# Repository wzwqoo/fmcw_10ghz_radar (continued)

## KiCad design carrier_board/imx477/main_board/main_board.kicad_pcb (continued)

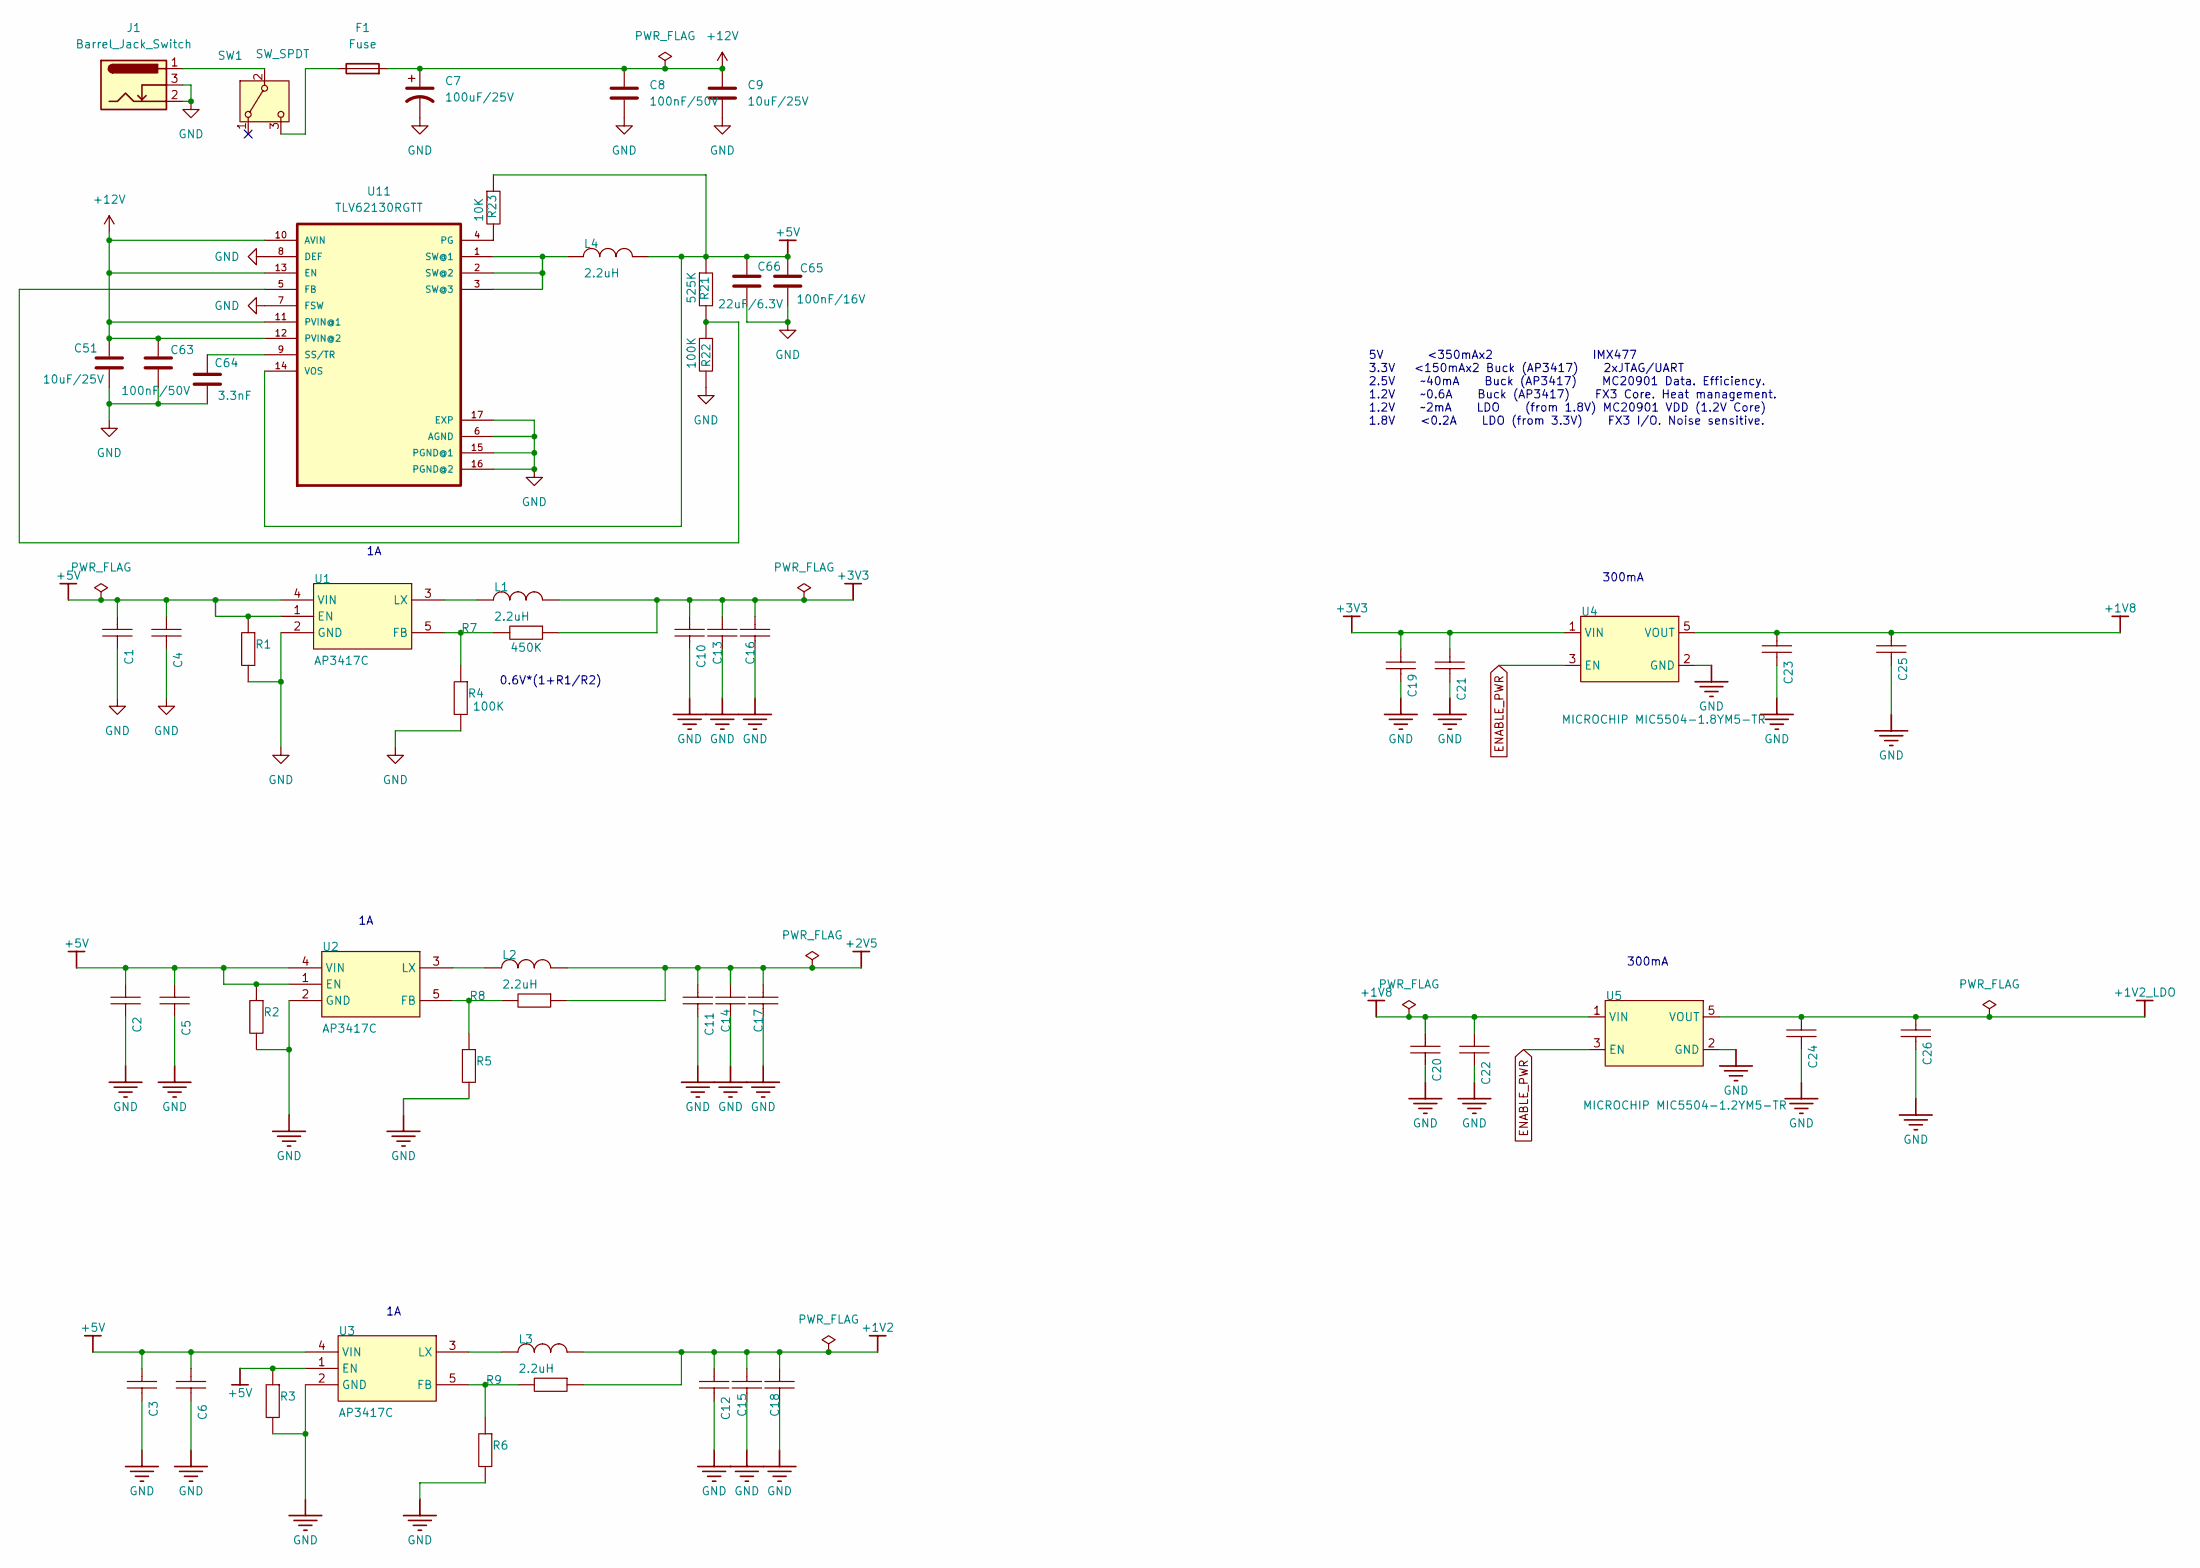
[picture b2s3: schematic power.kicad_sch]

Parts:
C1, C2, C3, C19, C20, C25, C26: 10uF; C_0603_1608Metric; RATINGS 50V; NP0; MANUFACTURER PART NUMBE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 06035A561JAT2A
C4, C5, C6, C10, C11, C12, C21, C22, C23, C24: 100nF; C_0603_1608Metric; TOLERANCE ±10%; RATINGS 16V; X7R; MANUFACTURER PART NUMBE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 CC0402KRX7R7BB103
C7: 100uF/25V; CP_Elec_6.3x5.7
C8, C63: 100nF/50V; C_0603_1608Metric
C9, C51: 10uF/25V; C_0603_1608Metric
C13, C14, C15, C16, C17, C18: 10uF; C_0603_1608Metric; TOLERANCE ±10%; RATINGS 16V; X5R; MANUFACTURER PART NUMBE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 EMK212BJ475KG-T
C64: 3.3nF; C_0603_1608Metric
C65: 100nF/16V; C_0603_1608Metric
C66: 22uF/6.3V; C_0603_1608Metric
F1: Fuse; Fuse_1812_4532Metric; Part# SMD1812P200TF16; LCSC Part # C20812
J1: Barrel_Jack_Switch; BarrelJack_CLIFF_FC681465S_SMT_Horizontal; Part# TBD
L1, L2, L3, L4: 2.2uH; L_Taiyo-Yuden_MD-4040; Part# CMLO0420H2R2MTT; LCSC Part # C438930
R1, R2, R3, R23: 10K; R_0603_1608Metric; RATINGS 1/16 W; TOLERANCE ±5%; MANUFACTURER PART NUMBE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 RC0402JR-073K3L
R4, R5, R6, R9, R22: 100K; R_0603_1608Metric; RATINGS 1/16 W; TOLERANCE ±5%; MANUFACTURER PART NUMBE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 RC0402JR-073K3L
R7: 450K; R_0603_1608Metric; RATINGS 1/16 W; TOLERANCE ±5%; MANUFACTURER PART NUMBE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 RC0402JR-073K3L
R8: 320K; R_0603_1608Metric; RATINGS 1/16 W; TOLERANCE ±5%; MANUFACTURER PART NUMBE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 RC0402JR-073K3L
R21: 525K; R_0603_1608Metric; RATINGS 1/16 W; TOLERANCE ±5%; MANUFACTURER PART NUMBE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 RC0402JR-073K3L
SW1: SW_SPDT; SW_SPDT_CK_JS102011SAQN; Part# JS102011SAQN; LCSC Part # C221660
U1, U2, U3: AP3417C; SOT-23-5; Part# AP3417CKTR-G1; LCSC Part # C500759
U4: MICROCHIP MIC5504-1.8YM5-TR; SOT-23-5; Part# MIC5504-1.8YM5-TR; LCSC Part # C626116
U5: MICROCHIP MIC5504-1.2YM5-TR; SOT-23-5; Part# MIC5504-1.8YM5-TR; LCSC Part # C626116
U11: TLV62130RGTT; VQFN-16-1EP_3x3mm_P0.5mm_EP1.6x1.6mm; DigiKey_Part_Number 296-32407-1-ND

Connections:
+1V2: C12.2, C15.1, C18.1, L3.2, R9.2; also elsewhere on the board
+1V2_LDO: C24.2, C26.1, U5.5 (VOUT); also elsewhere on the board
+1V8: C20.1, C22.2, C23.2, C25.1, U4.5 (VOUT), U5.1 (VIN); also elsewhere on the board
+2V5: C11.2, C14.1, C17.1, L2.2, R8.2; also elsewhere on the board
+3V3: C10.2, C13.1, C16.1, C19.1, C21.2, L1.2, R7.2, U4.1 (VIN); also elsewhere on the board
+5V: C1.1, C2.1, C3.1, C4.2, C5.2, C6.2, C65.1, C66.1, L4.2, R1.2, R2.2, R3.2, R21.2, R23.2, U1.1 (EN), U1.4 (VIN), U2.1 (EN), U2.4 (VIN), U3.1 (EN), U3.4 (VIN), U11.14 (VOS); also elsewhere on the board
+12V: C7.1, C8.1, C9.1, C51.1, C63.1, F1.2, U11.10 (AVIN), U11.11 (PVIN@1), U11.12 (PVIN@2), U11.13 (EN); also elsewhere on the board
ENABLE_PWR: U4.3 (EN), U5.3 (EN); also elsewhere on the board
GND: C1.2, C2.2, C3.2, C4.1, C5.1, C6.1, C7.2, C8.2, C9.2, C10.1, C11.1, C12.1, C13.2, C14.2, C15.2, C16.2, C17.2, C18.2, C19.2, C20.2, C21.1, C22.1, C23.1, C24.1, C25.2, C26.2, C51.2, C63.2, C64.2, C65.2, C66.2, J1.2, J1.3, R1.1, R2.1, R3.1, R4.1, R5.1, R6.1, R22.1, U1.2 (GND), U2.2 (GND), U3.2 (GND), U4.2 (GND), U5.2 (GND), U11.6 (AGND), U11.7 (FSW), U11.8 (DEF), U11.15 (PGND@1), U11.16 (PGND@2), U11.17 (EXP); also elsewhere on the board
unnamed: J1.1, SW1.2 (B)
unnamed: F1.1, SW1.3 (C)
unnamed: R4.2, R7.1, U1.5 (FB)
unnamed: L1.1, U1.3 (LX)
unnamed: R5.2, R8.1, U2.5 (FB)
unnamed: L2.1, U2.3 (LX)
unnamed: R6.2, R9.1, U3.5 (FB)
unnamed: L3.1, U3.3 (LX)
unnamed: R21.1, R22.2, U11.5 (FB)
unnamed: R23.1, U11.4 (PG)
unnamed: C64.1, U11.9 (SS/TR)
unnamed: L4.1, U11.1 (SW@1), U11.2 (SW@2), U11.3 (SW@3)

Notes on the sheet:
300mA
0.6V*(1+R1/R2)
5V <350mAx2 IMX477 3.3V <150mAx2 Buck (AP3417) 2xJTAG/UART 2.5V ~40mA Buck (AP3417) MC20901 Data. Efficiency. 1.2V ~0.6A Buck (AP3417) FX3 Core. Heat management. 1.2V ~2mA LDO (from 1.8V) MC20901 VDD (1.2V Core) 1.8V <0.2A LDO (from 3.3V) FX3 I/O. Noise sensitive.

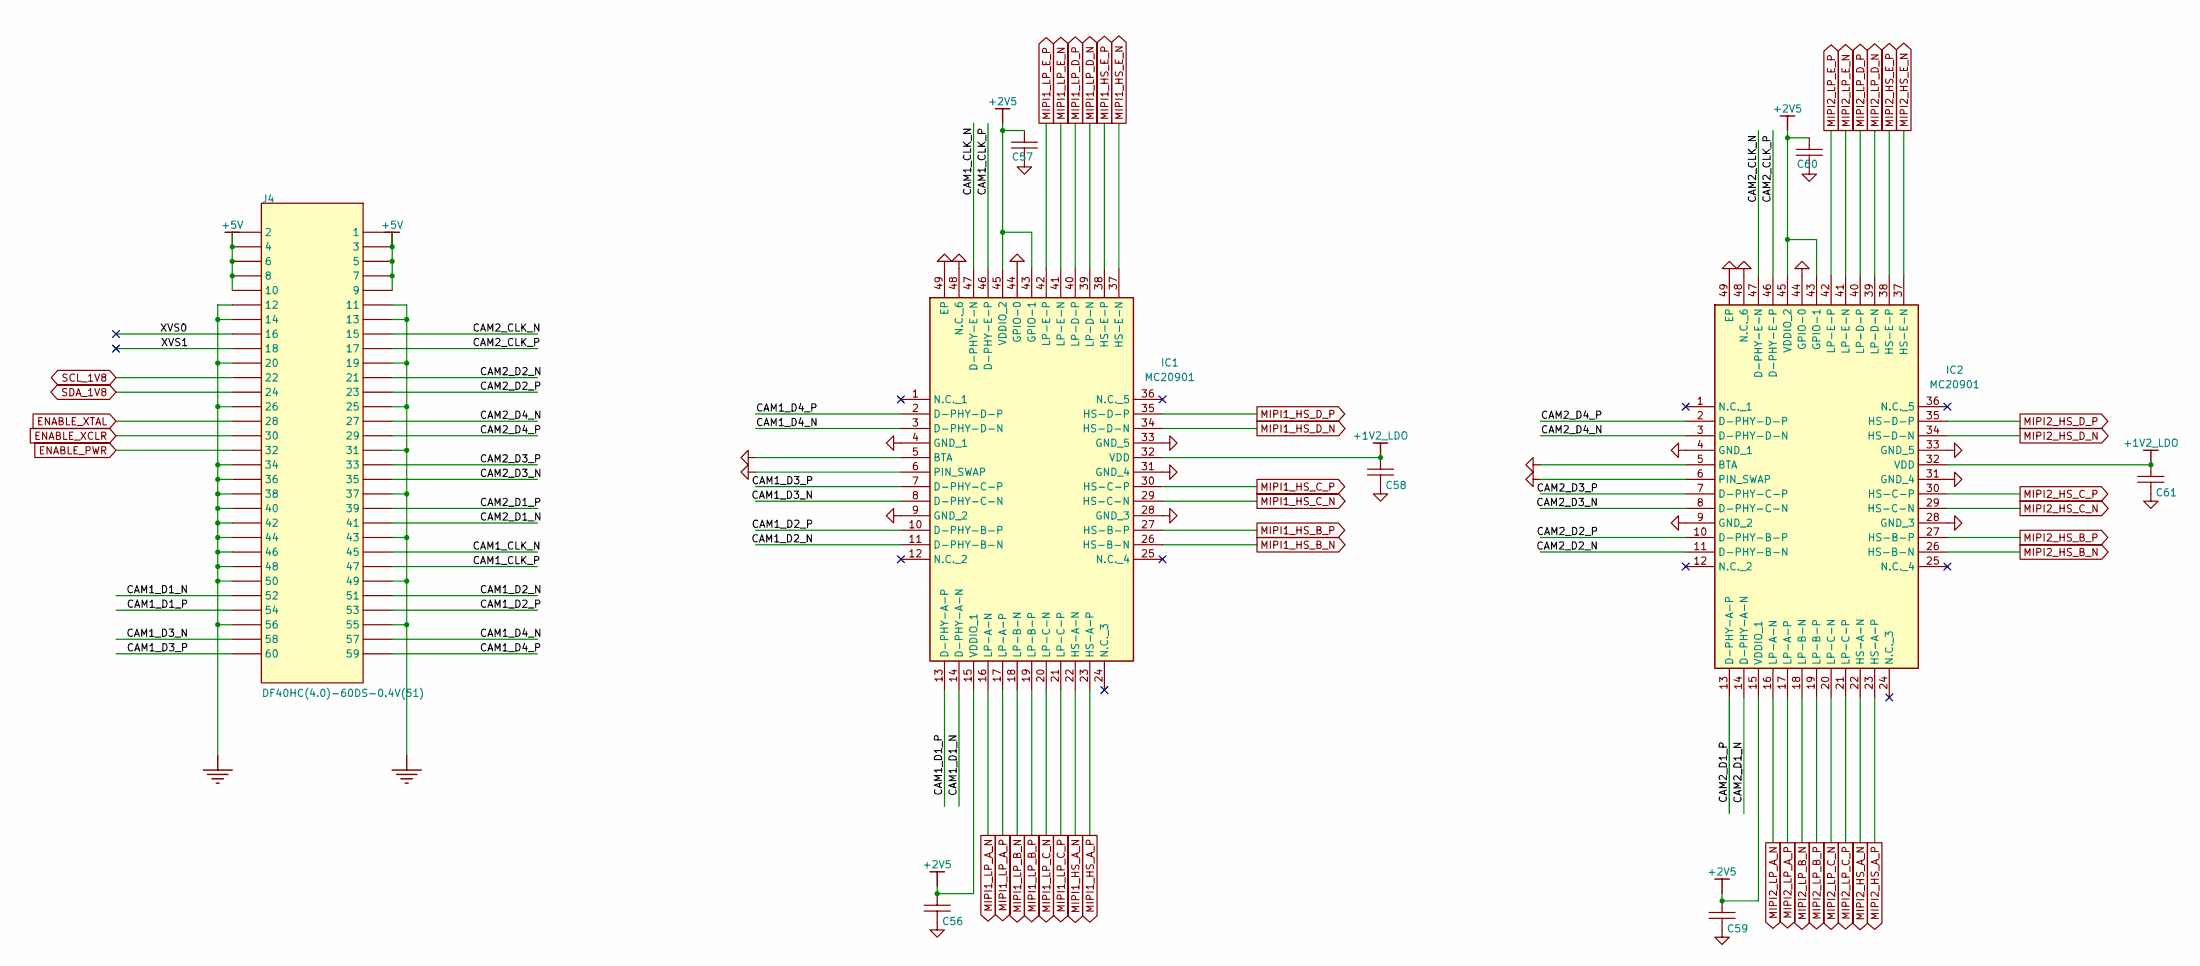
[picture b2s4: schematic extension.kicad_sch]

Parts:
C56, C57, C58, C59, C60, C61: 100nF; C_0603_1608Metric; TOLERANCE ±10%; RATINGS 16V; X7R; MANUFACTURER PART NUMBE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 CC0402KRX7R7BB103
IC1, IC2: MC20901; QFN50P700X700X80-49N-D; Manufacturer_Part_Number MC20901
J4: DF40HC(4.0)-60DS-0.4V(51); Hirose_DF40HC(4.0)-60DS-0.4V_2x30_P0.4mm

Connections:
+1V2_LDO: C58.2, C61.2, IC1.32 (VDD), IC2.32 (VDD); also elsewhere on the board
+2V5: C56.2, C57.2, C59.2, C60.2, IC1.15 (VDDIO_1), IC1.43 (GPIO-1), IC1.45 (VDDIO_2), IC2.15 (VDDIO_1), IC2.43 (GPIO-1), IC2.45 (VDDIO_2); also elsewhere on the board
+5V: J4.1, J4.2, J4.3, J4.4, J4.5, J4.6, J4.7, J4.8, J4.9, J4.10; also elsewhere on the board
/extension/CAM1_CLK_N: IC1.47 (D-PHY-E-N), J4.45
/extension/CAM1_CLK_P: IC1.46 (D-PHY-E-P), J4.47
/extension/CAM1_D1_N: IC1.14 (D-PHY-A-N), J4.52
/extension/CAM1_D1_P: IC1.13 (D-PHY-A-P), J4.54
/extension/CAM1_D2_N: IC1.11 (D-PHY-B-N), J4.51
/extension/CAM1_D2_P: IC1.10 (D-PHY-B-P), J4.53
/extension/CAM1_D3_N: IC1.8 (D-PHY-C-N), J4.58
/extension/CAM1_D3_P: IC1.7 (D-PHY-C-P), J4.60
/extension/CAM1_D4_N: IC1.3 (D-PHY-D-N), J4.57
/extension/CAM1_D4_P: IC1.2 (D-PHY-D-P), J4.59
/extension/CAM2_CLK_N: IC2.47 (D-PHY-E-N), J4.15
/extension/CAM2_CLK_P: IC2.46 (D-PHY-E-P), J4.17
/extension/CAM2_D1_N: IC2.14 (D-PHY-A-N), J4.41
/extension/CAM2_D1_P: IC2.13 (D-PHY-A-P), J4.39
/extension/CAM2_D2_N: IC2.11 (D-PHY-B-N), J4.21
/extension/CAM2_D2_P: IC2.10 (D-PHY-B-P), J4.23
/extension/CAM2_D3_N: IC2.8 (D-PHY-C-N), J4.35
/extension/CAM2_D3_P: IC2.7 (D-PHY-C-P), J4.33
/extension/CAM2_D4_N: IC2.3 (D-PHY-D-N), J4.27
/extension/CAM2_D4_P: IC2.2 (D-PHY-D-P), J4.29
/extension/XVS0: J4.16
/extension/XVS1: J4.18
ENABLE_PWR: J4.32; also elsewhere on the board
ENABLE_XCLR: J4.30; also elsewhere on the board
ENABLE_XTAL: J4.28; also elsewhere on the board
GND: C56.1, C57.1, C58.1, C59.1, C60.1, C61.1, IC1.4 (GND_1), IC1.5 (BTA), IC1.6 (PIN_SWAP), IC1.9 (GND_2), IC1.28 (GND_3), IC1.31 (GND_4), IC1.33 (GND_5), IC1.44 (GPIO-0), IC1.48 (N.C._6), IC1.49 (EP), IC2.4 (GND_1), IC2.5 (BTA), IC2.6 (PIN_SWAP), IC2.9 (GND_2), IC2.28 (GND_3), IC2.31 (GND_4), IC2.33 (GND_5), IC2.44 (GPIO-0), IC2.48 (N.C._6), IC2.49 (EP), J4.11, J4.12, J4.13, J4.14, J4.19, J4.20, J4.25, J4.26, J4.31, J4.34, J4.36, J4.37, J4.38, J4.40, J4.42, J4.43, J4.44, J4.46, J4.48, J4.49, J4.50, J4.55, J4.56; also elsewhere on the board
MIPI1_HS_A_N: IC1.22 (HS-A-N); also elsewhere on the board
MIPI1_HS_A_P: IC1.23 (HS-A-P); also elsewhere on the board
MIPI1_HS_B_N: IC1.26 (HS-B-N); also elsewhere on the board
MIPI1_HS_B_P: IC1.27 (HS-B-P); also elsewhere on the board
MIPI1_HS_C_N: IC1.29 (HS-C-N); also elsewhere on the board
MIPI1_HS_C_P: IC1.30 (HS-C-P); also elsewhere on the board
MIPI1_HS_D_N: IC1.34 (HS-D-N); also elsewhere on the board
MIPI1_HS_D_P: IC1.35 (HS-D-P); also elsewhere on the board
MIPI1_HS_E_N: IC1.37 (HS-E-N); also elsewhere on the board
MIPI1_HS_E_P: IC1.38 (HS-E-P); also elsewhere on the board
MIPI1_LP_A_N: IC1.16 (LP-A-N); also elsewhere on the board
MIPI1_LP_A_P: IC1.17 (LP-A-P); also elsewhere on the board
MIPI1_LP_B_N: IC1.18 (LP-B-N); also elsewhere on the board
MIPI1_LP_B_P: IC1.19 (LP-B-P); also elsewhere on the board
MIPI1_LP_C_N: IC1.20 (LP-C-N); also elsewhere on the board
MIPI1_LP_C_P: IC1.21 (LP-C-P); also elsewhere on the board
MIPI1_LP_D_N: IC1.39 (LP-D-N); also elsewhere on the board
MIPI1_LP_D_P: IC1.40 (LP-D-P); also elsewhere on the board
MIPI1_LP_E_N: IC1.41 (LP-E-N); also elsewhere on the board
MIPI1_LP_E_P: IC1.42 (LP-E-P); also elsewhere on the board
MIPI2_HS_A_N: IC2.22 (HS-A-N); also elsewhere on the board
MIPI2_HS_A_P: IC2.23 (HS-A-P); also elsewhere on the board
MIPI2_HS_B_N: IC2.26 (HS-B-N); also elsewhere on the board
MIPI2_HS_B_P: IC2.27 (HS-B-P); also elsewhere on the board
MIPI2_HS_C_N: IC2.29 (HS-C-N); also elsewhere on the board
MIPI2_HS_C_P: IC2.30 (HS-C-P); also elsewhere on the board
MIPI2_HS_D_N: IC2.34 (HS-D-N); also elsewhere on the board
MIPI2_HS_D_P: IC2.35 (HS-D-P); also elsewhere on the board
MIPI2_HS_E_N: IC2.37 (HS-E-N); also elsewhere on the board
MIPI2_HS_E_P: IC2.38 (HS-E-P); also elsewhere on the board
MIPI2_LP_A_N: IC2.16 (LP-A-N); also elsewhere on the board
MIPI2_LP_A_P: IC2.17 (LP-A-P); also elsewhere on the board
MIPI2_LP_B_N: IC2.18 (LP-B-N); also elsewhere on the board
MIPI2_LP_B_P: IC2.19 (LP-B-P); also elsewhere on the board
MIPI2_LP_C_N: IC2.20 (LP-C-N); also elsewhere on the board
MIPI2_LP_C_P: IC2.21 (LP-C-P); also elsewhere on the board
MIPI2_LP_D_N: IC2.39 (LP-D-N); also elsewhere on the board
MIPI2_LP_D_P: IC2.40 (LP-D-P); also elsewhere on the board
MIPI2_LP_E_N: IC2.41 (LP-E-N); also elsewhere on the board
MIPI2_LP_E_P: IC2.42 (LP-E-P); also elsewhere on the board
SCL_1V8: J4.22
SDA_1V8: J4.24

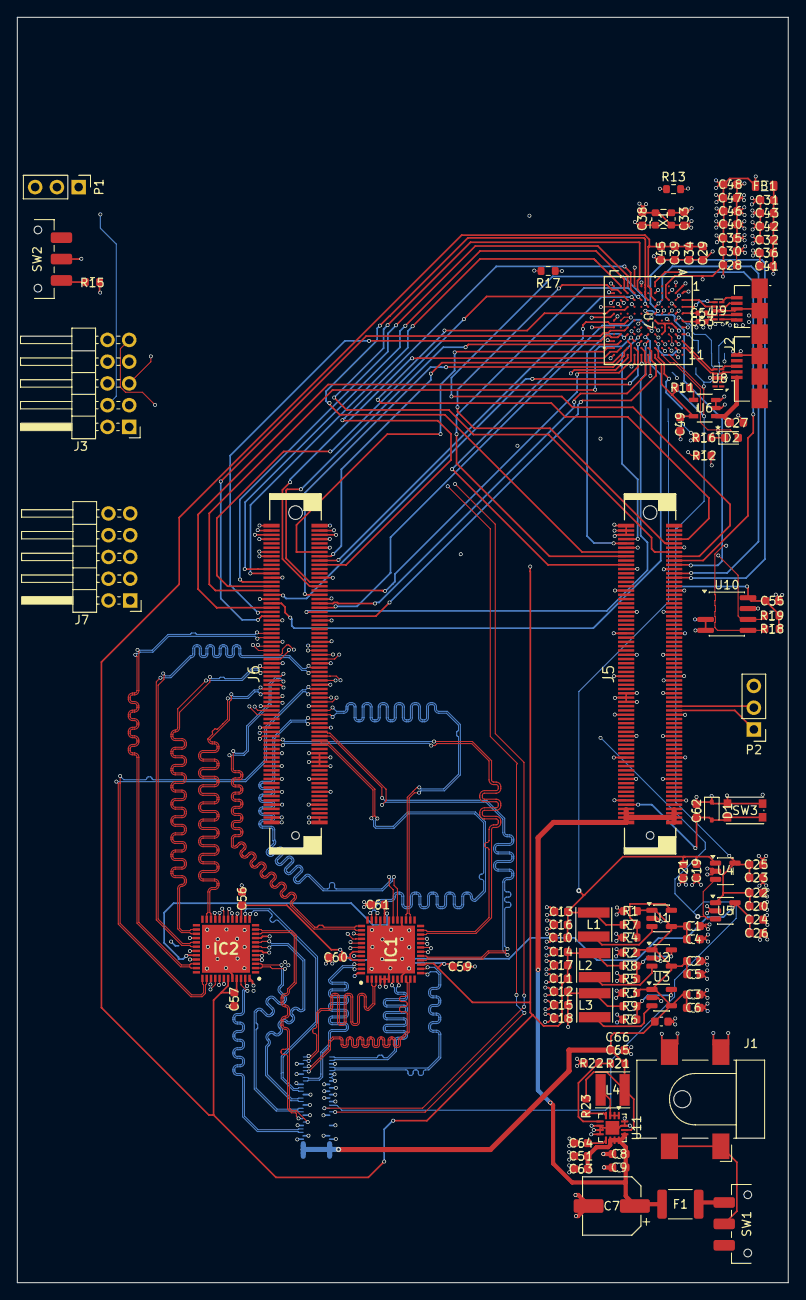
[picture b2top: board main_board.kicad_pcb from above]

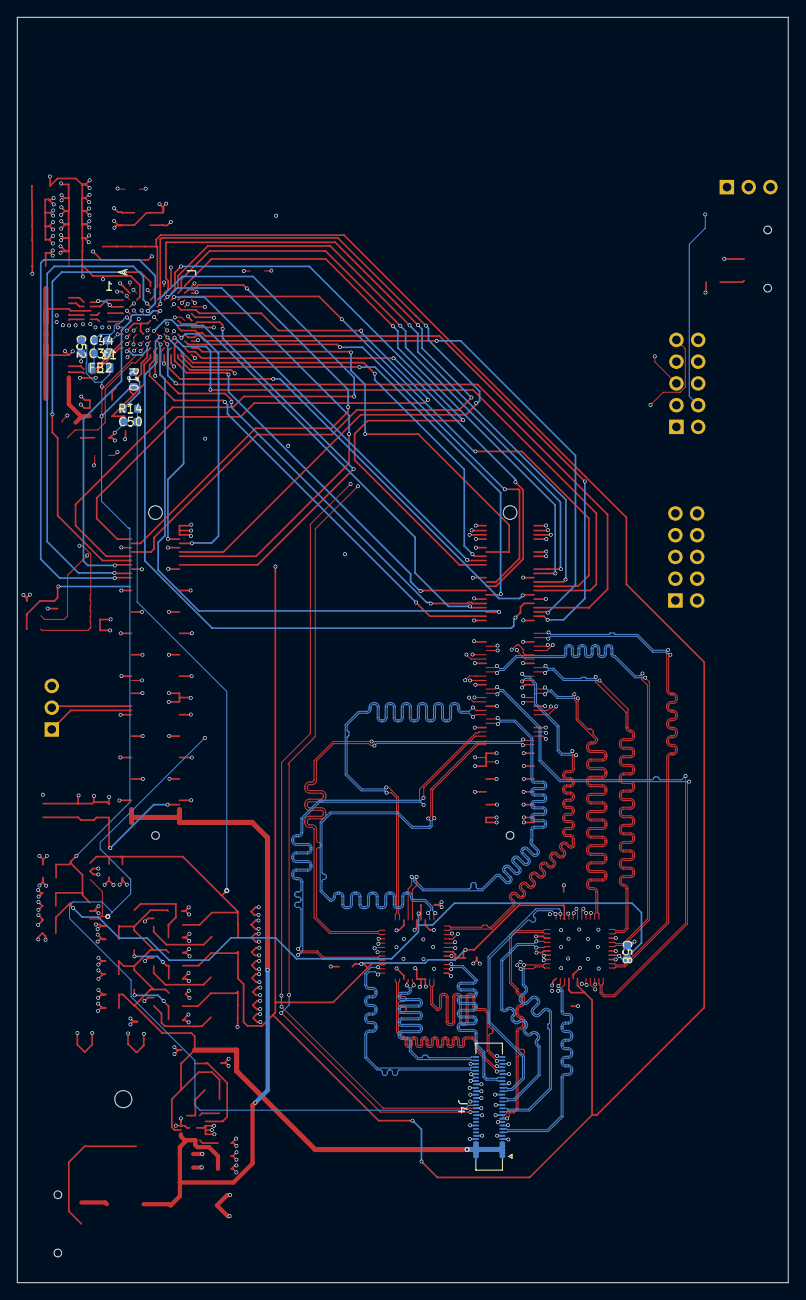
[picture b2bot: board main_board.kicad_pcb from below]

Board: 6 copper layers, 90.0 x 147.7 mm, 123 parts (9 on the bottom side), 165 nets.

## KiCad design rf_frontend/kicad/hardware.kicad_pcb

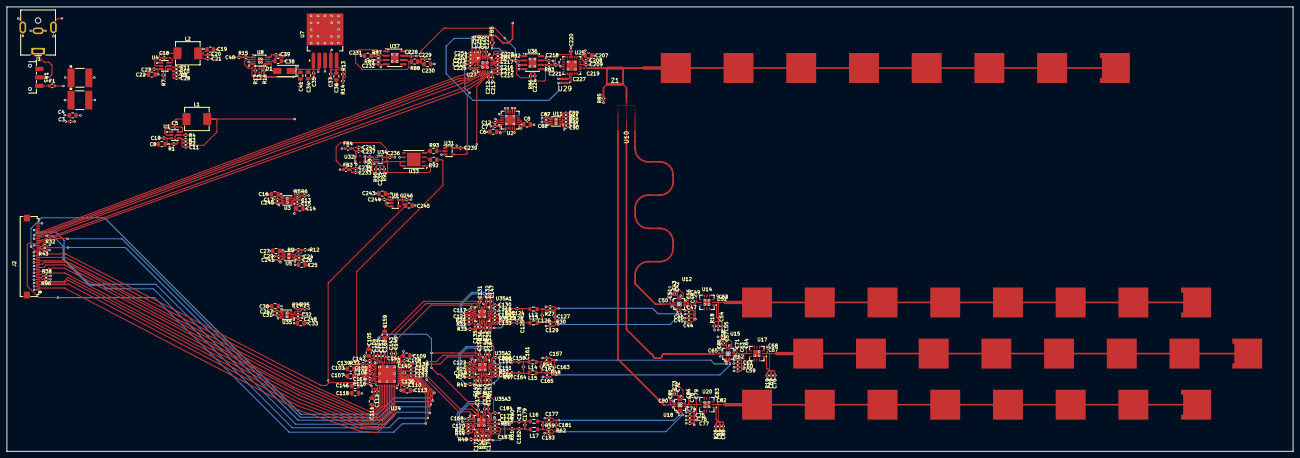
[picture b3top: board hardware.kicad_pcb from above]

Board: 4 copper layers, 377.3 x 130.4 mm, 351 parts (0 on the bottom side), 188 nets.

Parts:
AE1, AE2, AE3, AE4: Antenna; antenna
C1: 100uF; CAPC6153X670N
C2: dnp; CAPC6153X670N
C3, C5, C7, C10, C15, C17, C18, C20, C23, C26, C29, C31, C35, C37, C88, C91, C102, C104, C106, C108, C110, C112, C114, C116, C117, C119, C122, C130, C131, C134, C136, C137, C138, C140, C141, C143, C144, C145, C151, C155, C160, C166, C168, C173, C175, C184, C210, C212, C214, C217, C218, C228, C229, C232, C233, C236, C237, C239, C240, C241, C244, C246, C247, C248, C253, C255: 100nF; C_0402_1005Metric
C4, C14, C16, C25, C27, C30, C33, C34, C38, C41, C103, C105, C107, C109, C111, C113, C115, C146, C159, C243, C245: 10uF; C_0805_2012Metric
C6, C9, C22, C36, C230, C231: 22uF; C_0805_2012Metric
C8, C19: 47uF; C_0805_2012Metric
C11, C28: 75pF; C_0402_1005Metric
C12: 1uF; C_0402_1005Metric
C13, C21, C24, C32, C39, C89, C124, C128, C132, C147, C156, C158, C164, C167, C176, C178, C182, C185, C234, C235, C238, C242: 10nF; C_0402_1005Metric
C40, C125, C161, C179: 2.2nF; C_0402_1005Metric
C42, C57, C72: 2.2pF; C_0201_0603Metric
C43, C58, C73: 1uF/RF; C_0402_1005Metric
C44, C54, C59, C69, C74, C84: 100nF/RF; C_0402_1005Metric
C45, C60, C75, C208: 10nF/RF; C_0402_1005Metric
C46, C61, C76, C209: 100pF/RF; C_0402_1005Metric
C47, C55, C62, C70, C77, C85: 2.2pF/RF; C_0402_1005Metric
C48, C50, C52, C63, C65, C67, C78, C80, C82, C219, C226, C227: 22pF/RF; C_0201_0603Metric
C49, C53, C64, C68, C79, C83: 0.2pF/RF; C_0201_0603Metric
C51, C56, C66, C71, C81, C86: 0.15pF/Accu-P; C_0201_0603Metric
C87, C90: 10uF; C_0402_1005Metric
C118, C126, C150, C162, C172, C180: DNP; C_0402_1005Metric
C120, C121, C133, C135, C148, C149, C153, C169, C170, C171, C174, C187, C211, C213, C215, C216, C254, C256: 10pF; C_0402_1005Metric
C123, C127, C129, C157, C163, C165, C177, C181, C183, C225: 100pF; C_0402_1005Metric
C139: 5.6nF; C_0402_1005Metric
C142: 390pF; C_0402_1005Metric
C152, C154: 470nF; C_0402_1005Metric
C207: 2.2uF/Tantalum; C_0805_2012Metric
C220: 4pF; C_0402_1005Metric
C221: 820 pF; C_0402_1005Metric
C222: 22pF; C_0402_1005Metric
C223: 1.5 nF; C_0402_1005Metric
C224: 47nF; C_0402_1005Metric
D1: Schottky, ≥20V; D_SMA
F1: Fuse; Fuse_0603_1608Metric
FB3, FB4, FB5: 180Ω@100MHz; L_0603_1608Metric
J1: Barrel_Jack_Switch; BarrelJack_CUI_PJ-063AH_Horizontal
J2: Conn_01x40_Shielded; FPC-SMD_40P-P0.50_XUNPU_FPC-05FB-40PH20
L1, L2: 10uH; L_Sunlord_MWSA0602S
L3: 4.7nH; L_0402_1005Metric
L4, L5, L6, L7, L8, L9: stub; NetTie-2_SMD_Pad0.5mm
L12, L13, L14, L15, L16, L17: 2.2uH; L_0805_2012Metric
R1, R7: 511K; R_0402_1005Metric
R2, R8, R13, R17: 100K; R_0402_1005Metric
R3: 9.1K; R_0402_1005Metric
R4, R11: 105K; R_0402_1005Metric
R5, R9, R94: 3.57K; R_0402_1005Metric
R6, R12, R95: 1.15K; R_0402_1005Metric
R10: 19.4K; R_0402_1005Metric
R14: 9.01K; R_0402_1005Metric
R15: 20K; R_0402_1005Metric
R16: 1.2M; R_0402_1005Metric
R18, R19, R20: 510/RF; R_0402_1005Metric
R23, R24, R25, R26, R35, R36, R39, R42: 10k; R_0402_1005Metric
R27, R30, R45, R48, R59, R62: 49.9; R_0402_1005Metric
R28, R29, R31, R33, R34, R41, R44, R46, R47, R49, R60, R61: 550; R_0402_1005Metric
R32, R38, R43, R87, R89, R96: 10K; R_0402_1005Metric
R37: 1K; R_0402_1005Metric
R40, R52, R55, R66: 8.2k; R_0402_1005Metric
R50: 10.5K; R_0402_1005Metric
R51: 2K; R_0402_1005Metric
R82: 100; R_0402_1005Metric
R83: 680; R_0402_1005Metric
R84: 5.1k; R_0402_1005Metric
R85: 49.9/RF; R_0402_1005Metric
R86: 95.3; R_0402_1005Metric
R88: 22; R_0805_2012Metric
R90, R91: 470k; R_0402_1005Metric
R92, R93: 33; R_0805_2012Metric
SW1: SW_SPDT; SW_SPDT_CK_JS102011SAQN
U1, U4: TPS54302; SOT-23-6
U2: TPS7A4701xRGW; Texas_RGW0020A_VQFN-20-1EP_5x5mm_P0.65mm_EP3.15x3.15mm
U3, U5, U11, U35: TPS7A91; Texas_S-PDSO-N10_EP1.2x2mm
U6: MICROCHIP MIC5504-1.8YM5-TR; SOT-23-5
U7: MIC29302AWU; TO-263-5_TabPin3
U8: ADP1613ARMZ-R7; MSOP-8-1EP_3x3mm_P0.65mm_EP1.5x1.8mm
U10: 3 way splitter; splitter
U12, U15, U18: LTC5548IUDB-TRMPBF; QFN-12-1EP_3x3mm_P0.5mm_EP1.45x1.45mm
U14, U17, U20: PMA3-14LN+; VQFN-12-1EP_4x4mm_P0.8mm_EP2.1x2.1mm
U24: ADAR7251WBCSZ; LFCSP-VQ-48-1EP_7x7mm_P0.5mm
U25: HMC1163LP5ETR; LFCSP-32-1EP_5x5mm_P0.5mm_EP3.1x3.1mm
U27: ADF4159CCPZ-RL7; LFCSP-24-1EP_4x4mm_P0.5mm_EP2.3x2.3mm
U29: PAT1220-6dB; ATTN_PAT1220-C-1DB-T5
U31: SN74LVC1G17DBVR; SOT-23-5
U32: KT2520K; Oscillator_SMD_Kyocera_2520-6Pin_2.5x2.0mm
U33: NB3N551; DFN-8-1EP_6x5mm_P1.27mm_EP4x4mm
U34: NC7S04P5X; SOT-353_SC-70-5
U35A1, U35A2, U35A3: ADA4940-2; LFCSP-24-1EP_4x4mm_P0.5mm_EP2.5x2.5mm
U36, U37: ADA4625-1ARDZ; SOIC-8-1EP_3.9x4.9mm_P1.27mm_EP2.29x3mm
Z1: 4dB COUPLER; branchline

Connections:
+1V8: C114.1, C115.1, C116.1, C146.1, C212.1, C213.1, C214.1, C215.1, C239.1, C245.1, C246.1, U6.5 (VOUT), U24.19 (REGOUT_DIGITA), U24.21 (DVDD1), U24.24 (DVDD2), U27.18 (SDVDD), U27.19 (DVDD), U31.5 (VCC)
+3V3_A: C32.1, C33.1, C102.1, C103.1, C104.1, C105.1, C106.1, C107.1, C108.1, C109.1, C110.1, C111.1, C112.1, C113.1, C154.2, C210.1, C211.1, C248.1, C253.1, C254.1, C255.1, C256.1, FB5.1, R32.1, R43.1, R94.1, R96.1, U24.12 (AVDD2), U24.15 (PLLVDD), U24.18 (AVDD3), U24.25 (IOVDD1), U24.37 (IOVDD2), U24.48 (AVDD1), U27.6 (AVDD), U27.7 (AVDD), U27.8 (AVDD), U35.1 (OUT), U35.2 (OUT)
+3V3_D: C13.1, C14.1, C15.1, C243.1, C244.1, FB3.1, FB4.1, R5.1, U3.1 (OUT), U3.2 (OUT), U6.1 (VIN), U6.3 (EN)
+3V3_RF: C24.1, C25.1, C26.1, C42.1, C43.1, C57.1, C58.1, C72.1, C73.1, C117.1, C118.1, C119.1, C122.1, C150.1, C151.1, C168.1, C172.1, C173.1, R9.1, U5.1 (OUT), U5.2 (OUT), U12.7 (EN), U12.9 (VCC), U15.7 (EN), U15.9 (VCC), U18.7 (EN), U18.9 (VCC), U35A1.3 (+VS), U35A1.4 (+VS), U35A1.9 (+VS), U35A1.10 (+VS), U35A1.14 (~PD), U35A1.20 (~PD), U35A2.3 (+VS), U35A2.4 (+VS), U35A2.9 (+VS), U35A2.10 (+VS), U35A2.14 (~PD), U35A2.20 (~PD), U35A3.3 (+VS), U35A3.4 (+VS), U35A3.9 (+VS), U35A3.10 (+VS), U35A3.14 (~PD), U35A3.20 (~PD)
+3V6: C16.1, C19.1, C20.1, C21.1, C27.1, C28.2, C30.1, C38.1, C240.1, C241.1, C247.1, L2.2, L3.1, R8.2, U3.6 (SS_CTRL), U3.7 (EN), U3.9 (IN), U3.10 (IN), U5.6 (SS_CTRL), U5.7 (EN), U5.9 (IN), U5.10 (IN), U8.3 (EN), U8.6 (VIN), U35.6 (SS_CTRL), U35.7 (EN), U35.9 (IN), U35.10 (IN)
+5V: C89.1, C90.1, C91.1, C207.1, C208.1, C209.1, R50.1, U11.1 (OUT), U11.2 (OUT), U25.21 (VCC)
+6V: C8.1, C44.1, C45.1, C46.1, C47.1, C59.1, C60.1, C61.1, C62.1, C74.1, C75.1, C76.1, C77.1, C87.1, L4.1, L6.1, L8.1, U2.1 (OUT), U2.3 (SENSE/FB), U2.20 (OUT), U11.6 (SS_CTRL), U11.7 (EN), U11.9 (IN), U11.10 (IN)
+7V: C6.1, C7.1, C11.2, L1.2, R2.2, U2.13 (EN), U2.15 (IN), U2.16 (IN)
+12V: C1.1, C2.1, C3.1, C4.1, C9.1, C10.1, C22.1, C23.1, F1.2, R1.2, R7.2, U1.3 (VIN), U4.3 (VIN)
+15V: C36.1, C37.1, C218.1, C228.1, C231.1, R13.1, R87.1, U7.4 (VOUT), U36.7 (V+), U37.7 (V+)
+16V: C34.1, C35.1, C41.1, D1.1 (K), R16.1, U7.1 (EN), U7.2 (VIN)
/IF/AIN1N: C143.2, U35A1.19 (-OUT)
/IF/AIN1P: C145.2, U35A1.18 (+OUT)
/IF/AIN2N: C138.2, U35A2.19 (-OUT)
/IF/AIN2P: C141.2, U35A2.18 (+OUT)
/IF/AIN3N: C134.2, U35A3.19 (-OUT)
/IF/AIN3P: C137.2, U35A3.18 (+OUT)
/IF/VCOM: C130.1, C131.1, C155.1, C159.2, C160.2, C166.1, C175.1, C184.1, U24.8 (CM), U35A1.11 (VCOM), U35A1.17 (VCOM), U35A2.11 (VCOM), U35A2.17 (VCOM), U35A3.11 (VCOM), U35A3.17 (VCOM)
/RX/Antenna1: AE1.1 (A_1), C52.2
/RX/Antenna2: AE2.1 (A_1), C67.2
/RX/Antenna3: AE3.1 (A_1), C82.2
/RX/LO1: C50.2, U10.2 (PORT1)
/RX/LO2: C65.2, U10.3 (PORT2)
/RX/LO3: C80.2, U10.4 (PORT3)
/TX/ADF_REF_1V8: C225.1, U31.4 (Y)
/TX/VREF_raw: C232.1, R87.2, R89.1, U37.3 (+)
ADAR_CS_N: J2.25, R43.2, U24.41 (*SPI_SS)
ADAR_FAULT_N: J2.26, R32.2, U24.42 (*FAULT)
ADAR_RESET_N: J2.24, U24.43 (*RESET/*PWDN)
ADC_D0: J2.20, U24.26 (ADC_DOUT0)
ADC_D1: J2.18, U24.27 (ADC_DOUT1)
ADC_D2: J2.16, U24.28 (ADC_DOUT2/GPIO2)
ADC_D3: J2.14, U24.29 (ADC_DOUT3/GPIO1)
ADC_D4: J2.12, U24.30 (ADC_DOUT4)
ADC_D5: J2.10, U24.31 (ADC_DOUT5)
ADC_D6: J2.8, R38.1, R96.2, U24.32 (ADDR15/ADC_DOUT6)
ADC_D7: J2.6, U24.33 (FS_ADC/ADC_DOUT7)
ADC_REF: R92.1, U24.16 (XIN/MCLKIN)
ADF_CE_1V8: J2.34, U27.13 (CE)
ADF_LE_1V8: J2.30, U27.16 (LE)
ADF_MUXOUT_1V8: J2.29, U27.17 (MUXOUT)
ADF_TXDATA_1V8: J2.35, U27.12 (TXDATA)
CONV_START: J2.2, U24.35 (*CONV_START)
DATA_READY: J2.22, U24.22 (DATA_READY)
GND: C1.2, C2.2, C3.2, C4.2, C6.2, C7.2, C8.2, C9.2, C10.2, C12.2, C14.2, C15.2, C16.2, C17.2, C19.2, C20.2, C21.2, C22.2, C23.2, C25.2, C26.2, C27.2, C29.2, C30.2, C31.2, C33.2, C34.2, C35.2, C36.2, C37.2, C38.2, C39.2, C40.2, C41.2, C42.2, C43.2, C44.2, C45.2, C46.2, C47.2, C49.2, C51.2, C53.2, C54.2, C55.2, C56.2, C57.2, C58.2, C59.2, C60.2, C61.2, C62.2, C64.2, C66.2, C68.2, C69.2, C70.2, C71.2, C72.2, C73.2, C74.2, C75.2, C76.2, C77.2, C79.2, C81.2, C83.2, C84.2, C85.2, C86.2, C87.2, C88.2, C90.2, C91.2, C102.2, C103.2, C104.2, C105.2, C106.2, C107.2, C108.2, C109.2, C110.2, C111.2, C112.2, C113.2, C114.2, C115.2, C116.2, C117.2, C118.2, C119.2, C122.2, C123.1, C129.2, C130.2, C131.2, C139.2, C142.2, C146.2, C150.2, C151.2, C152.2, C155.2, C157.1, C159.1, C160.1, C165.2, C166.2, C168.2, C172.2, C173.2, C175.2, C177.1, C183.2, C184.2, C207.2, C208.2, C209.2, C210.2, C211.2, C212.2, C213.2, C214.2, C215.2, C216.2, C217.2, C218.2, C220.2, C221.2, C222.1, C223.2, C228.2, C229.2, C230.2, C231.2, C232.2, C233.2, C234.2, C235.2, C236.2, C237.2, C239.2, C240.2, C241.2, C242.2, C243.2, C244.2, C245.2, C246.2, C247.2, C248.2, C253.2, C254.2, C255.2, C256.2, J1.2, J1.3, J2.1, J2.3, J2.5, J2.7, J2.9, J2.11, J2.13, J2.15, J2.17, J2.19, J2.21, J2.23, J2.27, J2.31, J2.36, J2.40, R3.1, R4.1, R6.2, R10.1, R11.1, R12.2, R14.2, R17.2, R18.2, R19.2, R20.2, R38.2, R51.2, R84.2, R85.1, R89.2, R95.2, U1.1 (GND), U2.6 (3.2V), U2.7 (GND), U2.9 (0.8V), U2.10 (0.4V), U2.11 (0.2V), U2.21 (EP), U3.4 (GND), U3.11 (GND), U4.1 (GND), U5.4 (GND), U5.11 (GND), U6.2 (GND), U7.3 (GND), U8.4 (GND), U8.7 (FREQ), U8.9, U11.4 (GND), U11.11 (GND), U12.1 (GND), U12.4 (GND), U12.6 (GND), U12.8 (X2), U12.10 (GND), U12.12 (GND), U12.13, U14.13 (GND), U15.1 (GND), U15.4 (GND), U15.6 (GND), U15.8 (X2), U15.10 (GND), U15.12 (GND), U15.13, U17.13 (GND), U18.1 (GND), U18.4 (GND), U18.6 (GND), U18.8 (X2), U18.10 (GND), U18.12 (GND), U18.13, U20.13 (GND), U24.1 (AGND1), U24.9 (AGND2), U24.13 (PLLGND), U24.20 (DGND1), U24.23 (DGND2), U24.36 (DGND3), U24.49 (EP), U25.5 (GND), U25.11 (GND), U25.33 (EP), U27.1 (CPGND), U27.2 (AGND), U27.3 (AGND), U27.10 (DGND), U27.11 (SDGND), U27.25 (EPAD), U29.3, U31.3 (GND), U32.1 (GND), U32.3 (GND), U33.6 (GND), U34.3 (GND), U35.4 (GND), U35.11 (GND), U35A1.15 (-VS), U35A1.16 (-VS), U35A1.21 (-VS), U35A1.22 (-VS), U35A1.25, U35A2.15 (-VS), U35A2.16 (-VS), U35A2.21 (-VS), U35A2.22 (-VS), U35A2.25, U35A3.15 (-VS), U35A3.16 (-VS), U35A3.21 (-VS), U35A3.22 (-VS), U35A3.25, U36.4 (V-), U36.9 (EP), U37.4 (V-), U37.9 (EP)
IF1+: C123.2, C127.1, R27.1, U12.2 (IF+)
IF1-: C127.2, C129.1, R30.1, U12.3 (IF-)
IF2+: C157.2, C163.1, R45.1, U15.2 (IF+)
IF2-: C163.2, C165.1, R48.1, U15.3 (IF-)
IF3+: C177.2, C181.1, R59.1, U18.2 (IF+)
IF3-: C181.2, C183.1, R62.1, U18.3 (IF-)
LO_in: U10.1 (SUM), Z1.3
unnamed: AE4.1 (A_1), Z1.2
unnamed: C40.1, R15.2
unnamed: C124.1, R28.2
unnamed: C124.2, C125.1, L12.2
unnamed: C125.2, C128.2, L13.2
unnamed: C126.1, L12.1, R27.2
unnamed: C126.2, L13.1, R30.2
unnamed: C128.1, R29.2
unnamed: C132.1, R31.2
unnamed: C139.1, R37.2
unnamed: C147.1, R33.2
unnamed: C156.1, R34.2
unnamed: C158.1, R46.2
unnamed: C158.2, C161.1, L14.2
unnamed: C161.2, C164.2, L15.2
unnamed: C162.1, L14.1, R45.2
unnamed: C162.2, L15.1, R48.2
unnamed: C164.1, R47.2
unnamed: C167.1, R41.2
unnamed: C176.1, R44.2
unnamed: C178.1, R60.2
unnamed: C178.2, C179.1, L16.2
unnamed: C179.2, C182.2, L17.2
unnamed: C180.1, L16.1, R59.2
unnamed: C180.2, L17.1, R62.2
unnamed: C182.1, R61.2
unnamed: C185.1, R49.2
unnamed: C219.2, Z1.1
unnamed: C224.1, R86.1
unnamed: C224.2, R83.2, U36.6
unnamed: C226.1, U29.2
unnamed: C227.1, U29.1
unnamed: C235.1, R90.1, R91.2
unnamed: C238.1, R90.2, U34.2
unnamed: D1.2 (A), L3.2, U8.5 (SW)
unnamed: R85.2, Z1.4
unnamed: J1.1, SW1.2 (B)
unnamed: F1.1, SW1.3 (C)
unnamed: C5.1, U1.6 (BOOT)
unnamed: R1.1, R4.2, U1.5 (EN)
unnamed: C11.1, R2.1, R3.2, U1.4 (FB)
unnamed: C5.2, L1.1, U1.2 (SW)
unnamed: C12.1, U2.14 (NR)
unnamed: C13.2, R5.2, R6.1, U3.3 (FB)
unnamed: C17.1, U3.8 (NR/SS)
unnamed: C18.1, U4.6 (BOOT)
unnamed: R7.1, R11.2, U4.5 (EN)
unnamed: C28.1, R8.1, R10.2, U4.4 (FB)
unnamed: C18.2, L2.1, U4.2 (SW)
unnamed: C24.2, R9.2, R12.1, U5.3 (FB)
unnamed: C29.1, U5.8 (NR/SS)
unnamed: R13.2, R14.1, U7.5 (ADJ)
unnamed: R15.1, U8.1 (COMP)
unnamed: R16.2, R17.1, U8.2 (FB)
unnamed: C39.1, U8.8 (SS)
unnamed: C89.2, R50.2, R51.1, U11.3 (FB)
unnamed: C88.1, U11.8 (NR/SS)
unnamed: C50.1, C51.1, U12.11 (LO)
unnamed: C48.1, C56.1, U12.5 (RF)
unnamed: C54.1, C55.1, L5.1, R18.1, U14.1 (CURRENT_MIRROR)
unnamed: C52.1, C53.1, L5.2, U14.2 (RF-IN)
unnamed: C48.2, C49.1, L4.2, U14.8 (RF-OUT/VDD)
unnamed: C65.1, C66.1, U15.11 (LO)
unnamed: C63.1, C71.1, U15.5 (RF)
unnamed: C69.1, C70.1, L7.1, R19.1, U17.1 (CURRENT_MIRROR)
unnamed: C67.1, C68.1, L7.2, U17.2 (RF-IN)
unnamed: C63.2, C64.1, L6.2, U17.8 (RF-OUT/VDD)
unnamed: C80.1, C81.1, U18.11 (LO)
unnamed: C78.1, C86.1, U18.5 (RF)
unnamed: C84.1, C85.1, L9.1, R20.1, U20.1 (CURRENT_MIRROR)
unnamed: C82.1, C83.1, L9.2, U20.2 (RF-IN)
unnamed: C78.2, C79.1, L8.2, U20.8 (RF-OUT/VDD)
unnamed: C134.1, C136.2, U24.45 (AIN1N)
unnamed: C136.1, C137.1, U24.44 (AIN1P)
unnamed: C138.1, C140.2, U24.47 (AIN2N)
unnamed: C140.1, C141.1, U24.46 (AIN2P)
unnamed: C143.1, C144.2, U24.3 (AIN3N)
unnamed: C144.1, C145.1, U24.2 (AIN3P)
unnamed: C152.1, U24.10 (BIASN)
unnamed: C154.1, U24.11 (BIASP)
unnamed: C142.1, R37.1, U24.14 (PLLFILT)
unnamed: C219.1, U25.19 (RFOUT)
unnamed: C227.2, U25.12 (RFOUT/2)
unnamed: C220.1, C221.1, R83.1, U25.29 (VTUNE)
unnamed: C223.1, R82.1, U27.24 (CP)
unnamed: C225.2, U27.9 (REFIN)
unnamed: C226.2, U27.5 (RFINA)
unnamed: C222.2, U27.4 (RFINB)
unnamed: R84.1, U27.23 (RSET)
unnamed: C216.1, C217.1, FB5.2, U27.22 (VP)
unnamed: R93.1, U31.2 (A)
unnamed: C238.2, U32.4 (OUT)
unnamed: C237.1, C242.1, FB4.2, U32.6 (VDD)
unnamed: R91.1, U33.1 (ICLK), U34.4
unnamed: C233.1, C234.1, C236.1, FB3.2, U33.7 (VDD), U33.8 (OE), U34.5 (VCC)
unnamed: R92.2, U33.3 (Q2)
unnamed: R93.2, U33.4 (Q3)
unnamed: C32.2, R94.2, R95.1, U35.3 (FB)
unnamed: C31.1, U35.8 (NR/SS)
unnamed: C135.1, R36.1, U35A1.2 (+FB)
unnamed: C121.1, R24.1, R31.1, U35A1.24 (+IN)
unnamed: C121.2, R24.2, U35A1.23 (-FB)
unnamed: C135.2, R33.1, R36.2, U35A1.1 (-IN)
unnamed: C133.1, R35.1, U35A1.8 (+FB)
unnamed: C120.1, R23.1, R28.1, U35A1.6 (+IN)
unnamed: C147.2, U35A1.12 (+OUT)
unnamed: C120.2, R23.2, U35A1.5 (-FB)
unnamed: C133.2, R29.1, R35.2, U35A1.7 (-IN)
unnamed: C132.2, U35A1.13 (-OUT)
unnamed: C149.1, R39.1, U35A2.2 (+FB)
unnamed: C148.1, R25.1, R34.1, U35A2.24 (+IN)
unnamed: C148.2, R25.2, U35A2.23 (-FB)
unnamed: C149.2, R39.2, R41.1, U35A2.1 (-IN)
unnamed: C169.1, R52.1, U35A2.8 (+FB)
unnamed: C153.1, R40.1, R46.1, U35A2.6 (+IN)
unnamed: C167.2, U35A2.12 (+OUT)
unnamed: C153.2, R40.2, U35A2.5 (-FB)
unnamed: C169.2, R47.1, R52.2, U35A2.7 (-IN)
unnamed: C156.2, U35A2.13 (-OUT)
unnamed: C171.1, R42.1, U35A3.2 (+FB)
unnamed: C170.1, R26.1, R44.1, U35A3.24 (+IN)
unnamed: C170.2, R26.2, U35A3.23 (-FB)
unnamed: C171.2, R42.2, R49.1, U35A3.1 (-IN)
unnamed: C187.1, R66.1, U35A3.8 (+FB)
unnamed: C174.1, R55.1, R60.1, U35A3.6 (+IN)
unnamed: C185.2, U35A3.12 (+OUT)
unnamed: C174.2, R55.2, U35A3.5 (-FB)
unnamed: C187.2, R61.1, R66.2, U35A3.7 (-IN)
unnamed: C176.2, U35A3.13 (-OUT)
unnamed: R82.2, R86.2, U36.2 (-)
unnamed: R88.1, U37.2 (-), U37.6
SCLK_ADC: J2.4, U24.34 (SCLK_ADC)
SPI_MISO_3V3: J2.28, U24.38 (MISO)
SPI_MOSI_3V3: J2.32, U24.39 (MOSI), U27.15 (DATA)
SPI_SCLK_3V3: J2.33, U24.40 (SCLK), U27.14 (CLK)
VREF: C229.1, C230.1, R88.2, U36.3 (+)
